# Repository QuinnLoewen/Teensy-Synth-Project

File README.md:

# Teensy Synth Project

A polyphonic USB MIDI synthesizer featuring analog signal processing, built using the Teensy 4.1 microcontroller.

---

## 🚀 Overview

The **Teensy Synth Project** is a powerful and portable synthesizer leveraging the Teensy 4.1 for real-time polyphonic audio synthesis. This project combines high-quality digital synthesis with analog processing, offering an expressive and customizable musical instrument.

---

## 🎛️ Features

- **8-Voice Polyphony:** Simultaneously play up to 8 notes with dynamic voice allocation.
- **Multiple Modes:** Includes Polyphonic, Snap-Back (monophonic), and Arpeggiator modes.
- **Real-Time Controls:** Adjust ADSR envelope, LFO modulation, waveform selection, and built-in effects via hardware controls.
- **USB MIDI Integration:** Compatible with most USB MIDI controllers.
- **High-Fidelity Audio:** PCM5102A DAC, analog filtering, and effects for professional audio quality.
- **Visual Feedback:** Integrated TFT display shows waveform type, ADSR envelope, and LFO settings.

---

## 🛠️ Getting Started

### Prerequisites

- [Arduino IDE](https://www.arduino.cc/en/software) with [Teensyduino](https://www.pjrc.com/teensy/td_download.html)
- [VSCode](https://code.visualstudio.com/) with Arduino extension (optional but recommended)
- Required libraries:
  - Teensy Audio Library
  - USBHost_t36 Library
  - Adafruit GFX Library
  - Adafruit ST7735 Library

### Installation & Setup

1. **Clone the repository:**

```bash
git clone https://github.com/yourusername/Teensy-Synth-Project.git
cd Teensy-Synth-Project
Hardware Assembly:
Consult the Hardware/Schematics/ folder for circuit diagrams.
Assemble hardware components according to provided schematics and PCB layouts.
Software Installation:
Open the Synthesizer.ino file located in Software/ in Arduino IDE.
Set board type to Teensy 4.1.
Install required libraries through Arduino Library Manager.
Upload the sketch to the Teensy 4.1.

🎚️ Usage
Mode Button: Switch between Polyphonic, Snap-back, and Arpeggiator modes.
Waveform Button: Cycle through available waveform types (Sine, Square, Triangle, Sawtooth).
Effect Button: Enable or disable the global delay effect.
Potentiometers: Adjust Attack, Decay, Sustain, Release (ADSR envelope) and LFO parameters in real-time.
Display: TFT screen displays current mode, waveform type, ADSR envelope, and LFO parameters.

🧪 Testing & Results
Detailed test procedures and results are located in the Test_Results/ directory:
MIDI Latency Tests: Measured MIDI-to-audio latency (~1.2 ms average).
Polyphony Performance: Verified 8-voice polyphony with stable CPU usage (~55%).
Audio Quality Tests: Confirmed THD < 0.01% and SNR > 100 dB.
See the full report in Documentation/Final_Report.md.

Fork the repository.
Create your feature branch (git checkout -b feature/my-feature).
Commit your changes (git commit -m 'Add my feature').
Push to your branch (git push origin feature/my-feature).
Open a Pull Request describing your changes clearly.

Acknowledgements
Teensy Documentation
Teensy Audio Library
Adafruit GFX Library
Adafruit ST7735 Library
USB MIDI Specification

Future Enhancements
Additional audio effects (reverb, chorus, phaser)
Advanced modulation capabilities
Expanded visualizations and UI improvements on the TFT display
Optimization for increased polyphony (more than 8 voices)

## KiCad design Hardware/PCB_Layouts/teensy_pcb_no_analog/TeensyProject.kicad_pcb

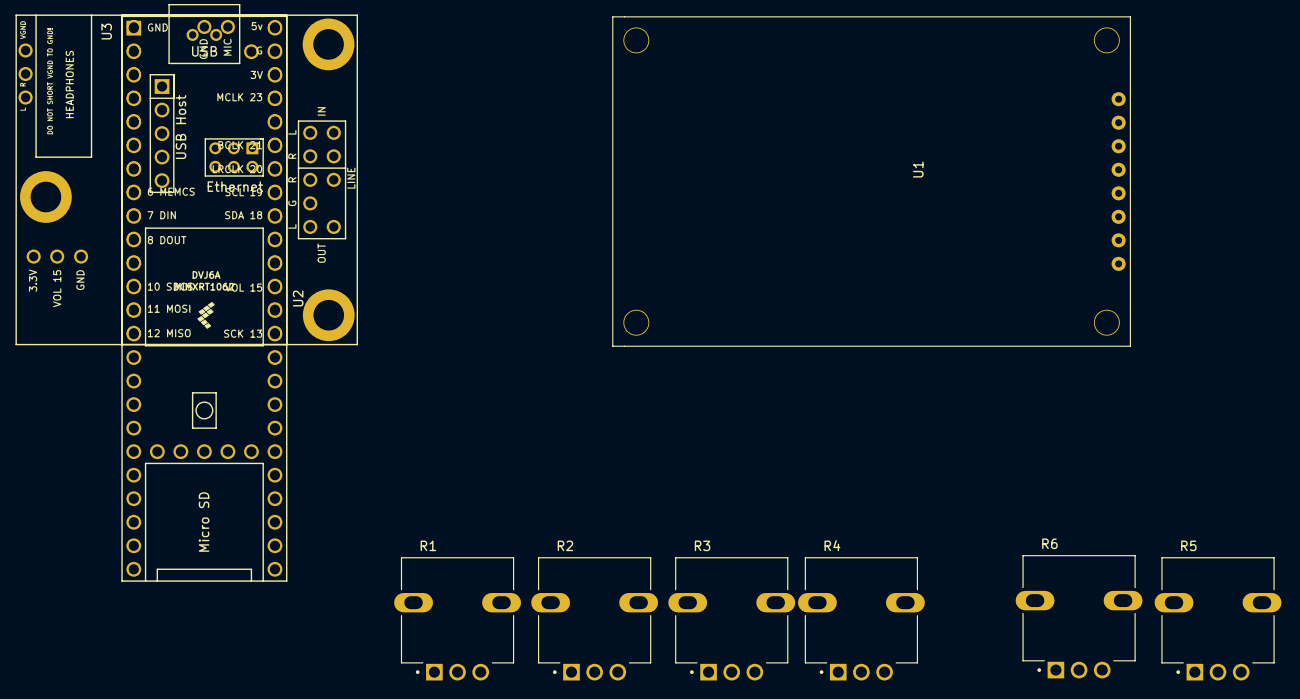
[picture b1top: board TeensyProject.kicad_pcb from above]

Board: 2 copper layers, 9 parts (0 on the bottom side), 29 nets, no tracks yet.

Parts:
R1, R2, R3, R4, R5, R6: P0915N-FC15BR100K; TRIM_P0915N-FC15BR100K
U1: Display_TFT_SPI_1.8
U2: Teensy4.1; Teensy41
U3: Teensy4.0_AudioShield_REVD; 4.0audioshield

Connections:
/3.3V: R1.3, R2.3, R3.3, R4.3, R5.3, R6.3, U1.2 (VDD), U2.15 (3V3)
/ADSR_A: R1.2, U2.30 (38_CS1_IN1)
/ADSR_D: R2.2, U2.31 (39_MISO1_OUT1A)
/ADSR_R: R4.2, U2.33 (41_A17)
/ADSR_S: R3.2, U2.32 (40_A16)
/I2S_BLCK: U2.43 (21_A7_RX5_BCLK1), U3.25 (21_A7_RX5_BCLK1)
/I2S_LRCLK: U2.42 (20_A6_TX5_LRCLK1), U3.24 (20_A6_TX5_LRCLK1)
/I2S_MCLK: U2.45 (23_A9_CRX1_MCLK1), U3.27 (23_A9_CRX1_MCLK1)
/I2S_RX: U2.9 (7_RX2_OUT1A), U3.9 (7_RX2_OUT1A)
/I2S_SCL: U2.41 (19_A5_SCL), U3.23 (19_A5_SCL0)
/I2S_SDA: U2.40 (18_A4_SDA), U3.22 (18_A4_SDA0)
/I2S_TX: U2.10 (8_TX2_IN1), U3.10 (8_TX2_IN1)
/LFO_DEPTH: R6.2, U2.17 (25_A11_RX6_SDA2)
/LFO_RATE: R5.2, U2.16 (24_A10_TX6_SCL2)
/SPI_CS: U2.12 (10_CS_MQSR), U3.12 (10_CS_MQSR)
/SPI_MOSI: U2.13 (11_MOSI_CTX1), U3.13 (11_MOSI_CTX1)
/SPI_SCK: U2.35 (13_SCK_LED), U3.17 (13_SCK_CRX1_LED)
GND: R1.1, R2.1, R3.1, R4.1, R5.1, R6.1, U1.1 (GND), U2.1 (GND), U3.1 (GND), U3.32 (LINE_OUT_GND)
unnamed: R1.S1 (SHIELD), R1.S2 (SHIELD)
unnamed: R2.S1 (SHIELD), R2.S2 (SHIELD)
unnamed: R3.S1 (SHIELD), R3.S2 (SHIELD)
unnamed: R4.S1 (SHIELD), R4.S2 (SHIELD)
unnamed: R5.S1 (SHIELD), R5.S2 (SHIELD)
unnamed: R6.S1 (SHIELD), R6.S2 (SHIELD)
unnamed: U1.7 (CS), U2.22 (30_CRX3)
unnamed: U1.6 (DC), U2.21 (29_TX7)
unnamed: U1.5 (RST), U2.20 (28_RX7)
unnamed: U1.3 (SCL), U2.19 (27_A13_SCK1)
unnamed: U1.4 (SDA), U2.18 (26_A12_MOSI1)

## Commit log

2025-03-11 Adding system files and base code
2025-03-11 Added updated file structures (not working)
    need to set the modular version of the files still, just a work in progress
2025-03-12 ADSR Working
    System Compiled and getting corrent ADSR info from printing
2025-03-12 Crea
2025-03-12 changes to readme
2025-03-12 added templated for test data
2025-03-12 signal mix and contributions
2025-03-12 adding teensy standalone component sheets without analog
2025-03-12 fixed file organization
2025-03-12 Added User Manuals
2025-03-12 added sys tests
2025-03-13 added changes to test results and added pictures
2025-03-15 Added Test Results
